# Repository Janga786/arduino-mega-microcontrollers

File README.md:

# ATmega2560 Microcontroller Projects

Coursework from CE 351 at Fort Lewis College: a custom ATmega2560 board I
designed in Eagle, and five folders of Arduino-IDE sketches. Most of the
sketches set up the ATmega2560's timers, ADC and USARTs by writing their
registers directly.
The sketches run on Fort Lewis College's ATmega2560 course board, which I
soldered and brought up. Everything here is small and course-sized; each
folder README says what the code does and what is not in the repo.

<p align="center">

&nbsp;

</p>

## Projects

| Folder | What it is |
| --- | --- |
| [`custom-mega-pcb/`](custom-mega-pcb/README.md) | 2-layer, 160 x 100 mm ATmega2560 board in Eagle 9.6: schematic, board file, Gerbers, drill and pick-and-place files. |
| [`bare-metal-adc-sampler/`](bare-metal-adc-sampler/README.md) | Timer1 starts an ADC conversion every 25 µs (40 kHz). After a threshold trigger the ADC interrupt stores 256 samples, and the main loop estimates the signal frequency from zero crossings. |
| [`ir-link-layer-protocol/`](ir-link-layer-protocol/README.md) | Serial messages over a 38 kHz IR carrier: Timer5 makes the carrier, Timer3 times the bits (2400 baud), USART1 receives. Messages carry source and destination addresses and a checksum. |
| [`interrupt-music-box/`](interrupt-music-box/README.md) | Three timer-interrupt sketches: a tone generator, a song player (Timer1 sets pitch, Timer3 sets note length) and a rhythm-copy game that times button presses. |
| [`tone-melody-player/`](tone-melody-player/README.md) | A button press plays a 25-note melody using software delay loops. |
| [`self-balancing-validation/`](self-balancing-validation/README.md) | Two bring-up sketches for a self-balancing robot: MPU-6050 gyro calibration and readout, and a TB6612FNG motor-driver spin test. |

## Building the sketches

1. Install Arduino IDE 2.x and the *Arduino AVR Boards* package.
2. Open the `.ino` file, select **Arduino Mega or Mega 2560**, pick the port, and upload.

The `gyro_test.ino` sketch needs the Adafruit MPU6050 library. To open the
PCB design, use Eagle 9.x or import it into KiCad.

## License

[MIT](LICENSE).

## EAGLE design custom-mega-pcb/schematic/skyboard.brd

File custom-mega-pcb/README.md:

# Custom ATmega2560 Board (Eagle)

A 2-layer, 160 x 100 mm ATmega2560 board I designed in Eagle 9.6 as my
CE 351 course project at Fort Lewis College. The Gerber job file names
the project `Jangas_Course_Project`. Many parts come from Arduino's
`UNO-TH_Rev3e` and `MEGA2560_Rev3e` Eagle libraries.

<p align="center">

&nbsp;

</p>

## What is on the board

From the pick-and-place file that goes with the Gerbers (`gerbers/PnP_top.txt`):

| Block | Part |
| --- | --- |
| MCU | ATmega2560 (TQFP-100) |
| Clock | 16 MHz ceramic resonator (CSTNE16M0V530000R0) |
| Regulator | AMS1117-5.0 |
| Audio | LM4862 audio amplifier |
| Other | reset/tactile switch, status LEDs, resistor networks, decoupling capacitors |

All parts are on the top side, so `PnP_bottom.txt` is empty.

## Files

```
custom-mega-pcb/
├── schematic/skyboard.sch, skyboard.brd   # Eagle design files
├── gerbers/                               # copper, mask, paste, silk, outline, drill, job file, pick-and-place
└── docs/
    ├── schematic.png                      # schematic of this board
    ├── layout.png                         # board layout of this board
    ├── layout_with_copper.png             # earlier CE 351 board (see note)
    ├── layout_traces_only.png             # earlier CE 351 board (see note)
    └── erc_clean.png                      # ERC window for the earlier board (see note)
```

## Limitations

- The `.sch`, `.brd` and Gerber files are not all from the same revision.
  The schematic also has a TB6612FNG motor driver and an ultrasonic-sensor
  header; the board file has a USB-B connector and an OPA344 op-amp; the
  Gerber pick-and-place adds the AMS1117 regulator.
- `schematic/skyboard.brd` has parts placed but no routed copper: 0 traces,
  0 vias and 79 airwires on 28 nets. The routed copper exists only in
  `docs/layout.png` (which still shows a few yellow airwires) and in the
  Gerbers.
- `layout_with_copper.png`, `layout_traces_only.png` and `erc_clean.png`
  show a different, earlier CE 351 board (an adjustable supply with an LED
  bar graph, built around an LT3080 and TLC274 op-amps). The ERC window in
  `erc_clean.png` lists 9 errors and 22 warnings for that board.
- The repo has no photo or test record of a fabricated copy of this board.

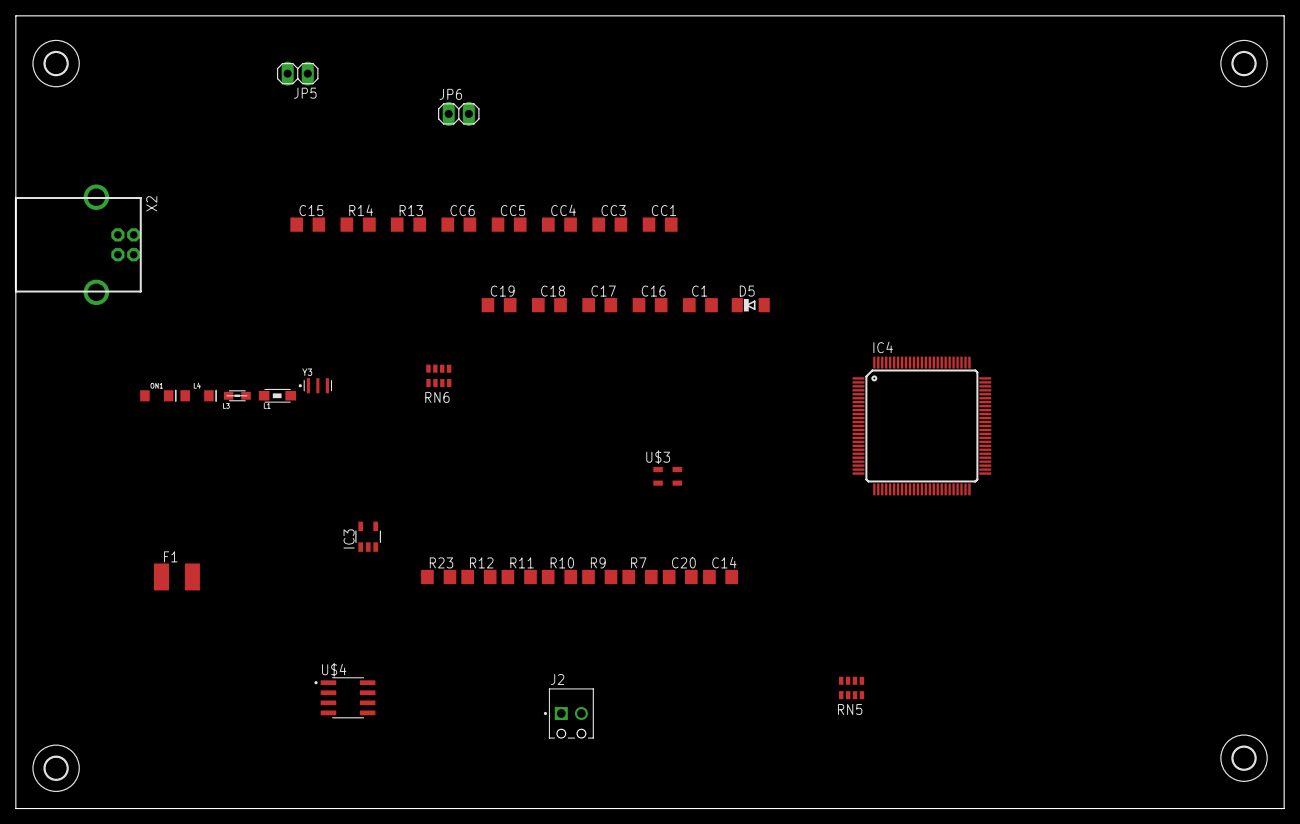
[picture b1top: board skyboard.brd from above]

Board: 2 copper layers, 160.0 x 100.0 mm, 42 parts (0 on the bottom side), 28 nets, no tracks yet.

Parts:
C1, C16, C17, C18, C19: 100n; SMARTPRJ_C1206
C14: 1u; SMARTPRJ_C1206
C15: 0.1u; SMARTPRJ_C1206
C20: 22p; SMARTPRJ_C1206
CC1: 10u; SMARTPRJ_C1206
CC3, CC4, CC5, CC6: 0.1u; SMARTPRJ_C1206
D5: CD1206-S01575; DIODE_MINIMELF
F1: MF-MSMF050-2 500mA; RCL_L1812
H1, H2, H3, H4: MOUNT-HOLE2.8; 2,8
IC3: OPA344N-SOT23; SOT23-5
IC4: ATMEGA2560-15AU; INTEGRATEDCIRCUITS_TQFP100
J2: 1725656; PHOENIX_1725656
JP5, JP6: 1X02
L1: BLM21; WUERTH-ELEKTRONIK_1206
L3: 10uH; INDUTTANZE_0805
L4: YELLOW; LED-1206
ON1: GREEN; LED-1206
R7, R9, R10: 2.2; R1206
R11, R12: 10k; R1206
R13, R14: 2.2K; R1206
R23: 1M; SMARTPRJ_R1206
RN5: 10k; RESISTOR-DIL_CAY16
RN6: 1k; RESISTOR-DIL_CAY16
U$3: MY_RGB; GM1WA55311A
U$4: MYLM4862; MYSOIC8
X2: USB-B_TH; SMARTPRJ_PN61729
Y3: CSTNE16M0V530000R0; OSC_CSTNE16M0V530000R0

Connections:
AREF: C18.2, IC4.98
BLUE: IC4.15, R10.1
GND: C1.1, C14.1, C16.1, C17.1, C18.1, C19.1, C20.1, CC1.2, CC3.2, CC4.2, CC5.2, IC3.2, IC4.11, IC4.32, IC4.62, IC4.81, IC4.99, L1.1, L4.C, ON1.C, U$4.1, U$4.7, X2.4, Y3.2
GREEN: IC4.16, R9.1
unnamed: CC6.1, R13.1, R14.2
unnamed: R10.2, U$3.3
unnamed: ON1.A, RN6.3
unnamed: R9.2, U$3.4
unnamed: R7.2, U$3.1
unnamed: C14.2, U$4.2, U$4.3
unnamed: R11.2, R12.1, U$4.4
unnamed: C15.2, R11.1
unnamed: J2.2, R12.2, U$4.5
unnamed: J2.1, U$4.8
unnamed: JP6.1, R13.2
unnamed: CC5.1, IC3.3, R14.1
unnamed: CC6.2, IC3.1, IC3.4, JP5.1
unnamed: C19.2, IC4.100, L3.1
unnamed: L4.A, RN6.4
PB7: IC4.26, RN6.5
PH5: IC4.17, R7.1
PRE: C15.1, JP5.2
RESET: C20.2, D5.A, IC4.30, RN5.8
SUPPLY1_+5V: C1.2, C16.2, C17.2, CC1.1, CC3.1, CC4.1, D5.C, F1.2, IC3.5, IC4.10, IC4.31, IC4.61, IC4.80, L3.2, RN5.1, RN6.6, U$3.2, U$4.6
UNSHIELD: L1.2, X2.P$1, X2.P$2
XTAL1: IC4.34, R23.1, Y3.3
XTAL2: IC4.33, R23.2, Y3.1
XUSB: F1.1, X2.1

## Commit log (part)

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2026-04-29 Initial release: six microcontroller projects on the ATmega2560
    A curated portfolio of standalone embedded-systems projects targeting
    the Arduino Mega 2560 (ATmega2560 @ 16 MHz):
    - custom-mega-pcb/ "Skyboard" — a 4-layer Arduino-Mega-class
    PCB designed in Eagle CAD with
    production-ready Gerbers, drill files,
    and pick-and-place outputs ready for a

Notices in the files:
parts and their libraries:
SparkFun-LED: Licensing: Creative Commons ShareAlike 4.0 International - https://creativecommons.org/licenses/by-sa/4.0
